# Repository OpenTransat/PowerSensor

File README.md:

# Power Sensor

* Measures voltage &amp; current of each solar panel separately

* Measures voltage &amp; current of a (backup) battery

* Uses INA219 for measurement

* Communicates via I2C

There are two thermally isolated regions on the PCB as the Schottky diodes generate heat. The PCB will be potted in a heat conductive epoxy while keeping the regions isolated. The potted Power Sensor will be attached to aluminum structure that will be cooled down by the surrounding water.

## Boat Hardware Scheme

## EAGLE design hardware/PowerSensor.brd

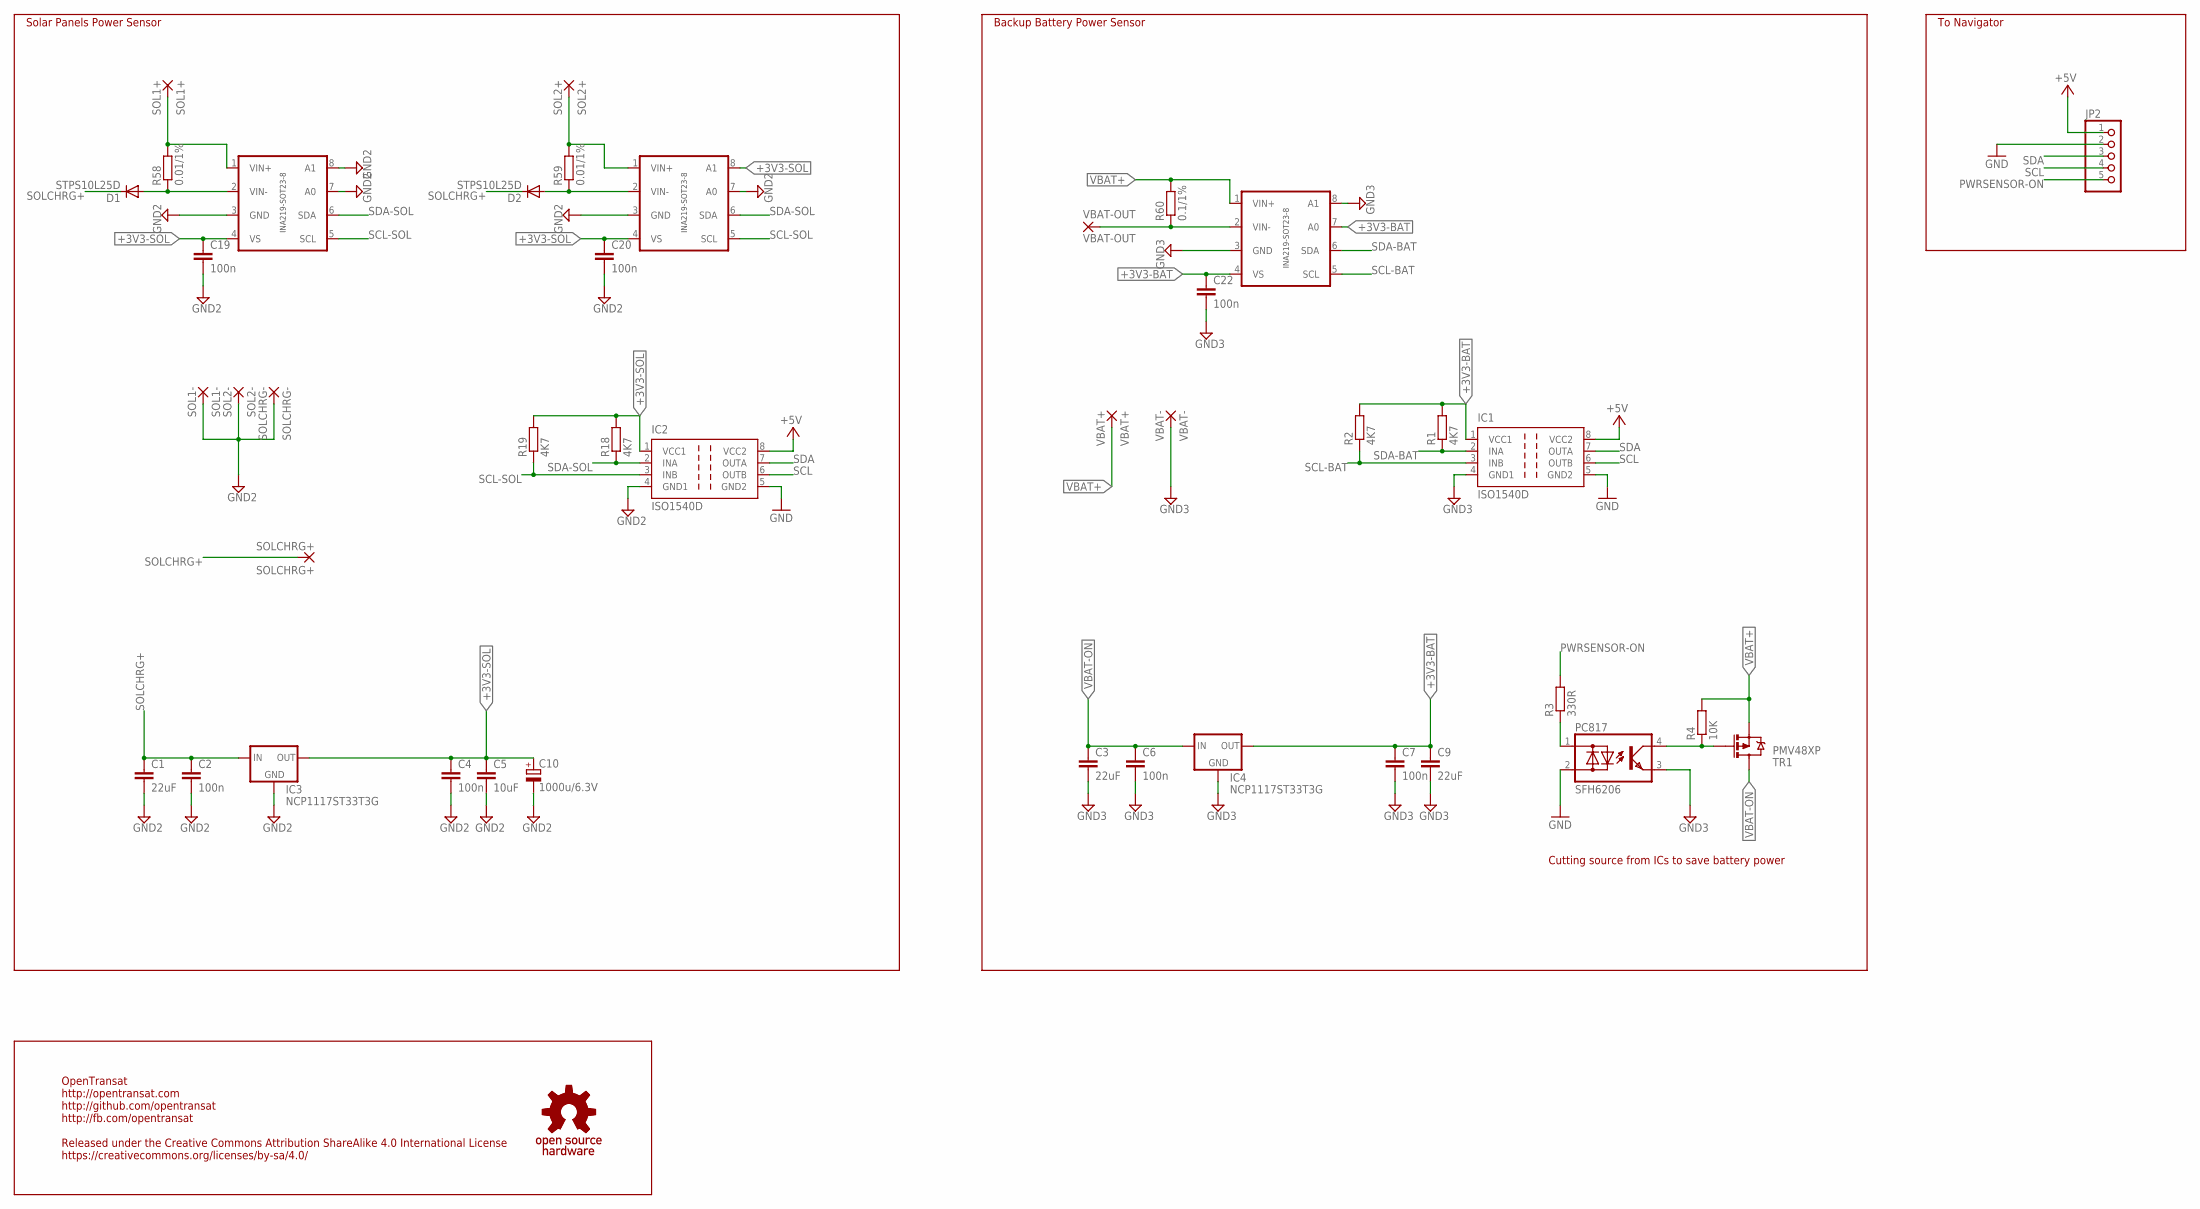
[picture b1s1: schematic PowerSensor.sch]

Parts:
C1, C3, C9: 22uF; C1210
C2, C4, C6, C7, C19, C20, C22: 100n; C0603
C5: 10uF; C1206
C10: 1000u/6.3V; E3,5-8
D1, D2: STPS10L25D; TO220ACS
IC1, IC2: ISO1540D; SO-08
IC3, IC4: NCP1117ST33T3G; SOT223
JP2: PINHD-1X5; 1X05
PC817: SFH6206; DIL4-SMD
R1, R2, R18, R19: 4K7; R0603
R3: 330R; R0603
R4: 10K; R0603
R58, R59: 0.01/1%; R2512
R60: 0.1/1%; R2512
SOL1+: SOL1+; SMD5,08-10,16
SOL1-: SOL1-; SMD5,08-10,16
SOL2+: SOL2+; SMD5,08-10,16
SOL2-: SOL2-; SMD5,08-10,16
SOLCHRG+: SOLCHRG+; SMD5,08-10,16
SOLCHRG-: SOLCHRG-; SMD5,08-10,16
TR1: PMV48XP; SOT23-3
U$1, U$4, U$5: INA219-SOT23-8; SOT23-8
U$2: OSHW; OSHWM
VBAT+: VBAT+; SMD2,54-5,08
VBAT-: VBAT-; SMD2,54-5,08
VBAT-OUT: VBAT-OUT; SMD2,54-5,08

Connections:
+3V3-BAT: C7.1, C9.1, C22.1, IC1.1 (VCC1), IC4.2 (OUT), IC4.4 (OUT), R1.2, R2.2, U$5.4 (VS), U$5.7 (A0)
+3V3-SOL: C4.1, C5.1, C10.+, C19.1, C20.1, IC2.1 (VCC1), IC3.2 (OUT), IC3.4 (OUT), R18.2, R19.2, U$1.4 (VS), U$4.4 (VS), U$4.8 (A1)
+5V: IC1.8 (VCC2), IC2.8 (VCC2), JP2.1
GND: IC1.5 (GND2), IC2.5 (GND2), JP2.2, PC817.2 (AC2)
GND2: C1.2, C2.2, C4.2, C5.2, C10.-, C19.2, C20.2, IC2.4 (GND1), IC3.1 (GND), SOL1-.1, SOL2-.1, SOLCHRG-.1, U$1.3 (GND), U$1.7 (A0), U$1.8 (A1), U$4.3 (GND), U$4.7 (A0)
GND3: C3.2, C6.2, C7.2, C9.2, C22.2, IC1.4 (GND1), IC4.1 (GND), PC817.3 (E), U$5.3 (GND), U$5.8 (A1), VBAT-.1
unnamed: D1.A, R58.1, U$1.2 (VIN-)
unnamed: D2.A, R59.1, U$4.2 (VIN-)
unnamed: R58.2, SOL1+.1, U$1.1 (VIN+)
unnamed: R59.2, SOL2+.1, U$4.1 (VIN+)
unnamed: R60.1, U$5.2 (VIN-), VBAT-OUT.1
unnamed: PC817.1 (AC1), R3.1
unnamed: PC817.4 (C), R4.1, TR1.1 (G)
PWRSENSOR-ON: JP2.5, R3.2
SCL: IC1.6 (OUTB), IC2.6 (OUTB), JP2.4
SCL-BAT: IC1.3 (INB), R2.1, U$5.5 (SCL)
SCL-SOL: IC2.3 (INB), R19.1, U$1.5 (SCL), U$4.5 (SCL)
SDA: IC1.7 (OUTA), IC2.7 (OUTA), JP2.3
SDA-BAT: IC1.2 (INA), R1.1, U$5.6 (SDA)
SDA-SOL: IC2.2 (INA), R18.1, U$1.6 (SDA), U$4.6 (SDA)
SOLCHRG+: C1.1, C2.1, D1.C, D2.C, IC3.3 (IN), SOLCHRG+.1
VBAT+: R4.2, R60.2, TR1.2 (S), U$5.1 (VIN+), VBAT+.1
VBAT-ON: C3.1, C6.1, IC4.3 (IN), TR1.3 (D)

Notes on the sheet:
Solar Panels Power Sensor
Backup Battery Power Sensor
To Navigator
OpenTransat http://opentransat.com http://github.com/opentransat http://fb.com/opentransat Released under the Creative Commons Attribution ShareAlike 4.0 International License https://creativecommons.org/licenses/by-sa/4.0/
Cutting source from ICs to save battery power

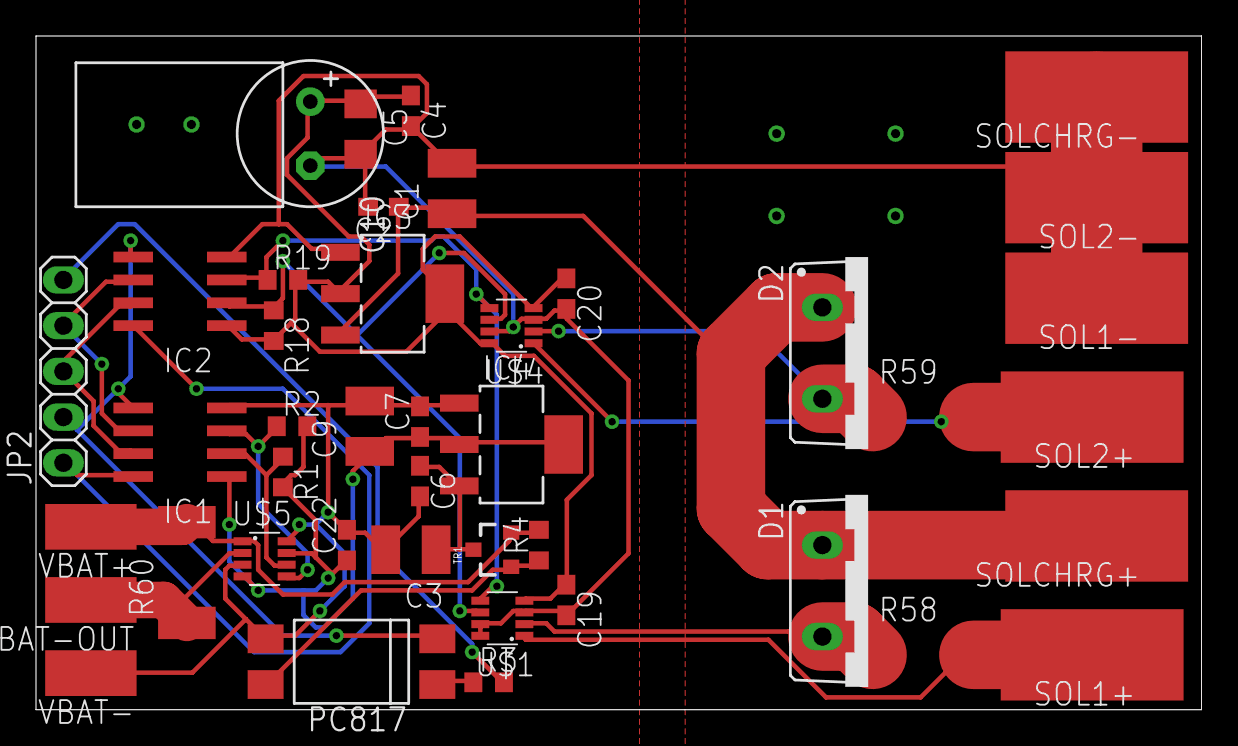
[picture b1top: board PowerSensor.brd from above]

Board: 2 copper layers, 64.8 x 37.4 mm, 43 parts (0 on the bottom side), 23 nets.
